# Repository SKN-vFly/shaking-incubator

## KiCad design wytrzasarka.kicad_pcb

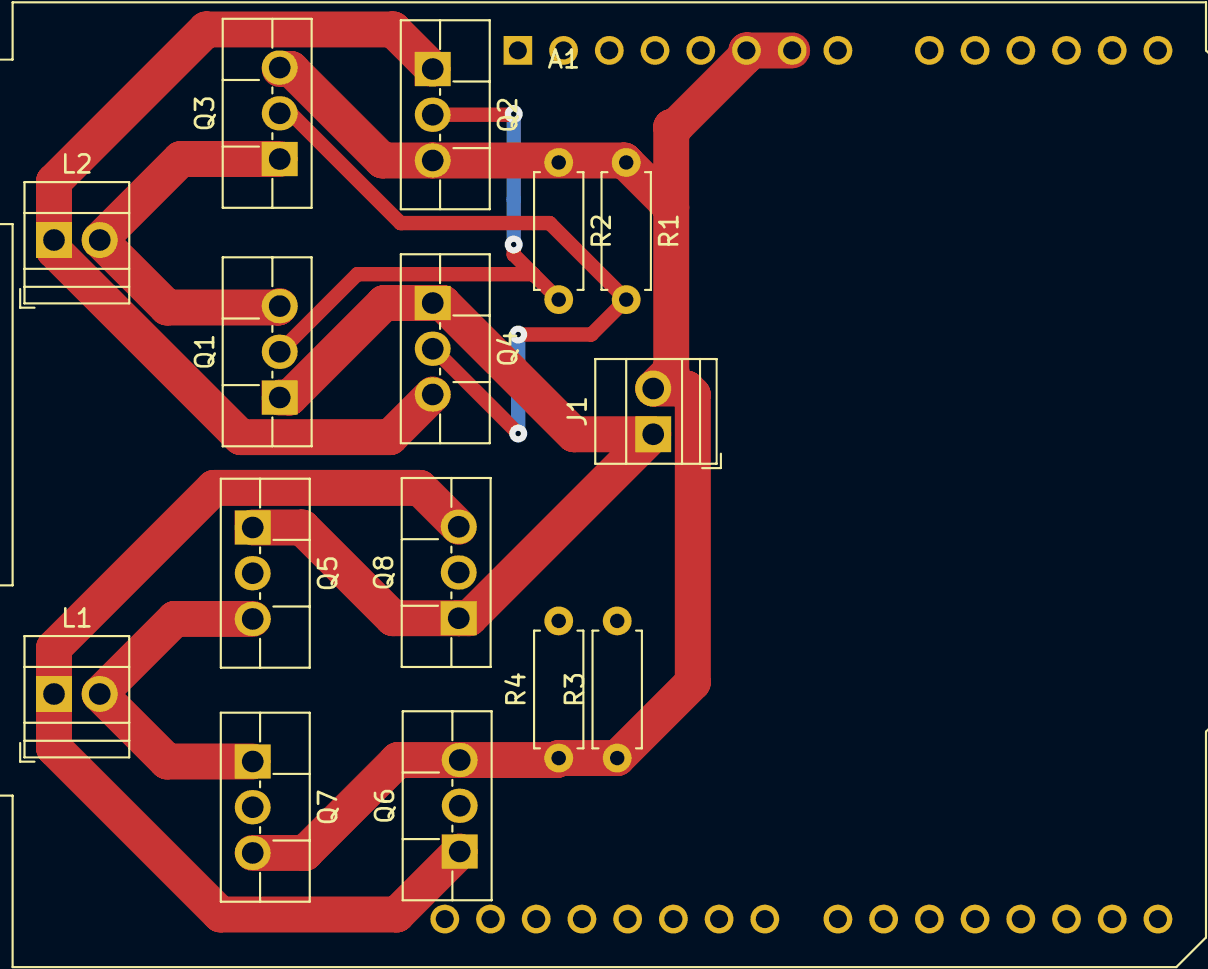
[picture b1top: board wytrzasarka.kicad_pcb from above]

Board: 2 copper layers, 16 parts (0 on the bottom side), 10 nets.

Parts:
A1: Arduino_UNO_R2
J1: Screw_Terminal_01x02; TerminalBlock_Xinya_XY308-2.54-2P_1x02_P2.54mm_Horizontal
L1, L2: L; TerminalBlock_Xinya_XY308-2.54-2P_1x02_P2.54mm_Horizontal
Q1, Q2, Q3, Q4, Q5, Q6, Q7, Q8: NMOS; TO-220F-3_Vertical
R1, R2, R3, R4: 10K; R_Axial_DIN0207_L6.3mm_D2.5mm_P7.62mm_Horizontal

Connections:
/Output pins: A1.28 (D13), Q7.2 (G), Q8.2 (G), R3.2
/bramka1/clock2: A1.25 (D10), Q3.2 (G), Q4.2 (G), R1.2
/bramka1/clock3: A1.26 (D11), Q1.2 (G), Q2.2 (G), R2.2
/bramka1/coil2: L2.2, Q1.3 (S), Q3.1 (D)
/bramka1/coil3: L2.1, Q2.1 (D), Q4.3 (S)
/bramka/clock1: A1.27 (D12), Q5.2 (G), Q6.2 (G), R4.2
/bramka/coil0: L1.2, Q5.3 (S), Q7.1 (D)
/bramka/coil1: L1.1, Q6.1 (D), Q8.3 (S)
GND: A1.6 (GND), A1.7 (GND), A1.29 (GND), J1.2, Q2.3 (S), Q3.3 (S), Q6.3 (S), Q7.3 (S), R1.1, R2.1, R3.1, R4.1
VCC: J1.1, Q1.1 (D), Q4.1 (D), Q5.1 (D), Q8.1 (D)

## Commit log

2024-11-28 hall sensor voltage and pinout
2024-11-28 hall sensors pinout
2024-11-28 render
2024-12-02 wojciechowe działania (poprawiono podschematy, dodano footprinty, pierwsze podejscie do pcb)
2024-12-03 something has happened
2024-12-04 hell
